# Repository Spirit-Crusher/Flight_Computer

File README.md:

MCU: https://www.microchip.com/en-us/product/pic32mz2048efh100

GPS: https://pt.mouser.com/ProductDetail/u-blox/NEO-M8J?qs=sGAEpiMZZMu3sxpa5v1qrlhWywTP0pnuh%2BmP8LamgMg%3D

Data logging for GPS: https://pt.mouser.com/ProductDetail/Microchip-Technology/SST26VF032BT-104I-SM?qs=wzzOUr4NhYqzScXXOX3HBA%3D%3D

IMU (acel + gyro): https://pt.mouser.com/ProductDetail/STMicroelectronics/LSM6DS3TR-C?qs=sGAEpiMZZMs29kr3d%2BndIw9GjDKvhDTryg6A%2FwXJ%2FS4%3D

Magnetómetro: https://pt.mouser.com/ProductDetail/STMicroelectronics/LIS3MDLTR?qs=hnsWAVXnr6EbLE48dGN9Pg%3D%3D

Altímetro (temp incluída): https://pt.mouser.com/ProductDetail/Measurement-Specialties/MS560702BA03-50?qs=sGAEpiMZZMtiz6SYu%2FjtS3nI99Ya1op5gwRqEQTw8xo%3D

Buzzer: https://www.digikey.com/en/products/detail/ole-wolff-electronics-inc/OWMB-858540SA-40-15/16735155

Antena(GPS): ???

Telemetry transmiter/antenna: ???

Data logging (flash memory IC): https://pt.mouser.com/ProductDetail/Winbond/W25Q128JVSIQ?qs=qSfuJ%252Bfl%2Fd6tLXvPR4fl9w%3D%3D

Power management IC: https://pt.mouser.com/ProductDetail/Texas-Instruments/INA219BIDR?qs=1WmUhT%2FVMINyGsXNJcdD5Q%3D%3D (maybe BMS board would be better)

Pyro channels and others

Ver redundância 

# DONE
- [x] Decoupling capacitors for each IC and basic conections.
- [ ] Sorting out power (all 3V3 or anything else needed?)
- [ ] Reverse polarity protection (which approach should I use?)
- [x] Programmer pins connector

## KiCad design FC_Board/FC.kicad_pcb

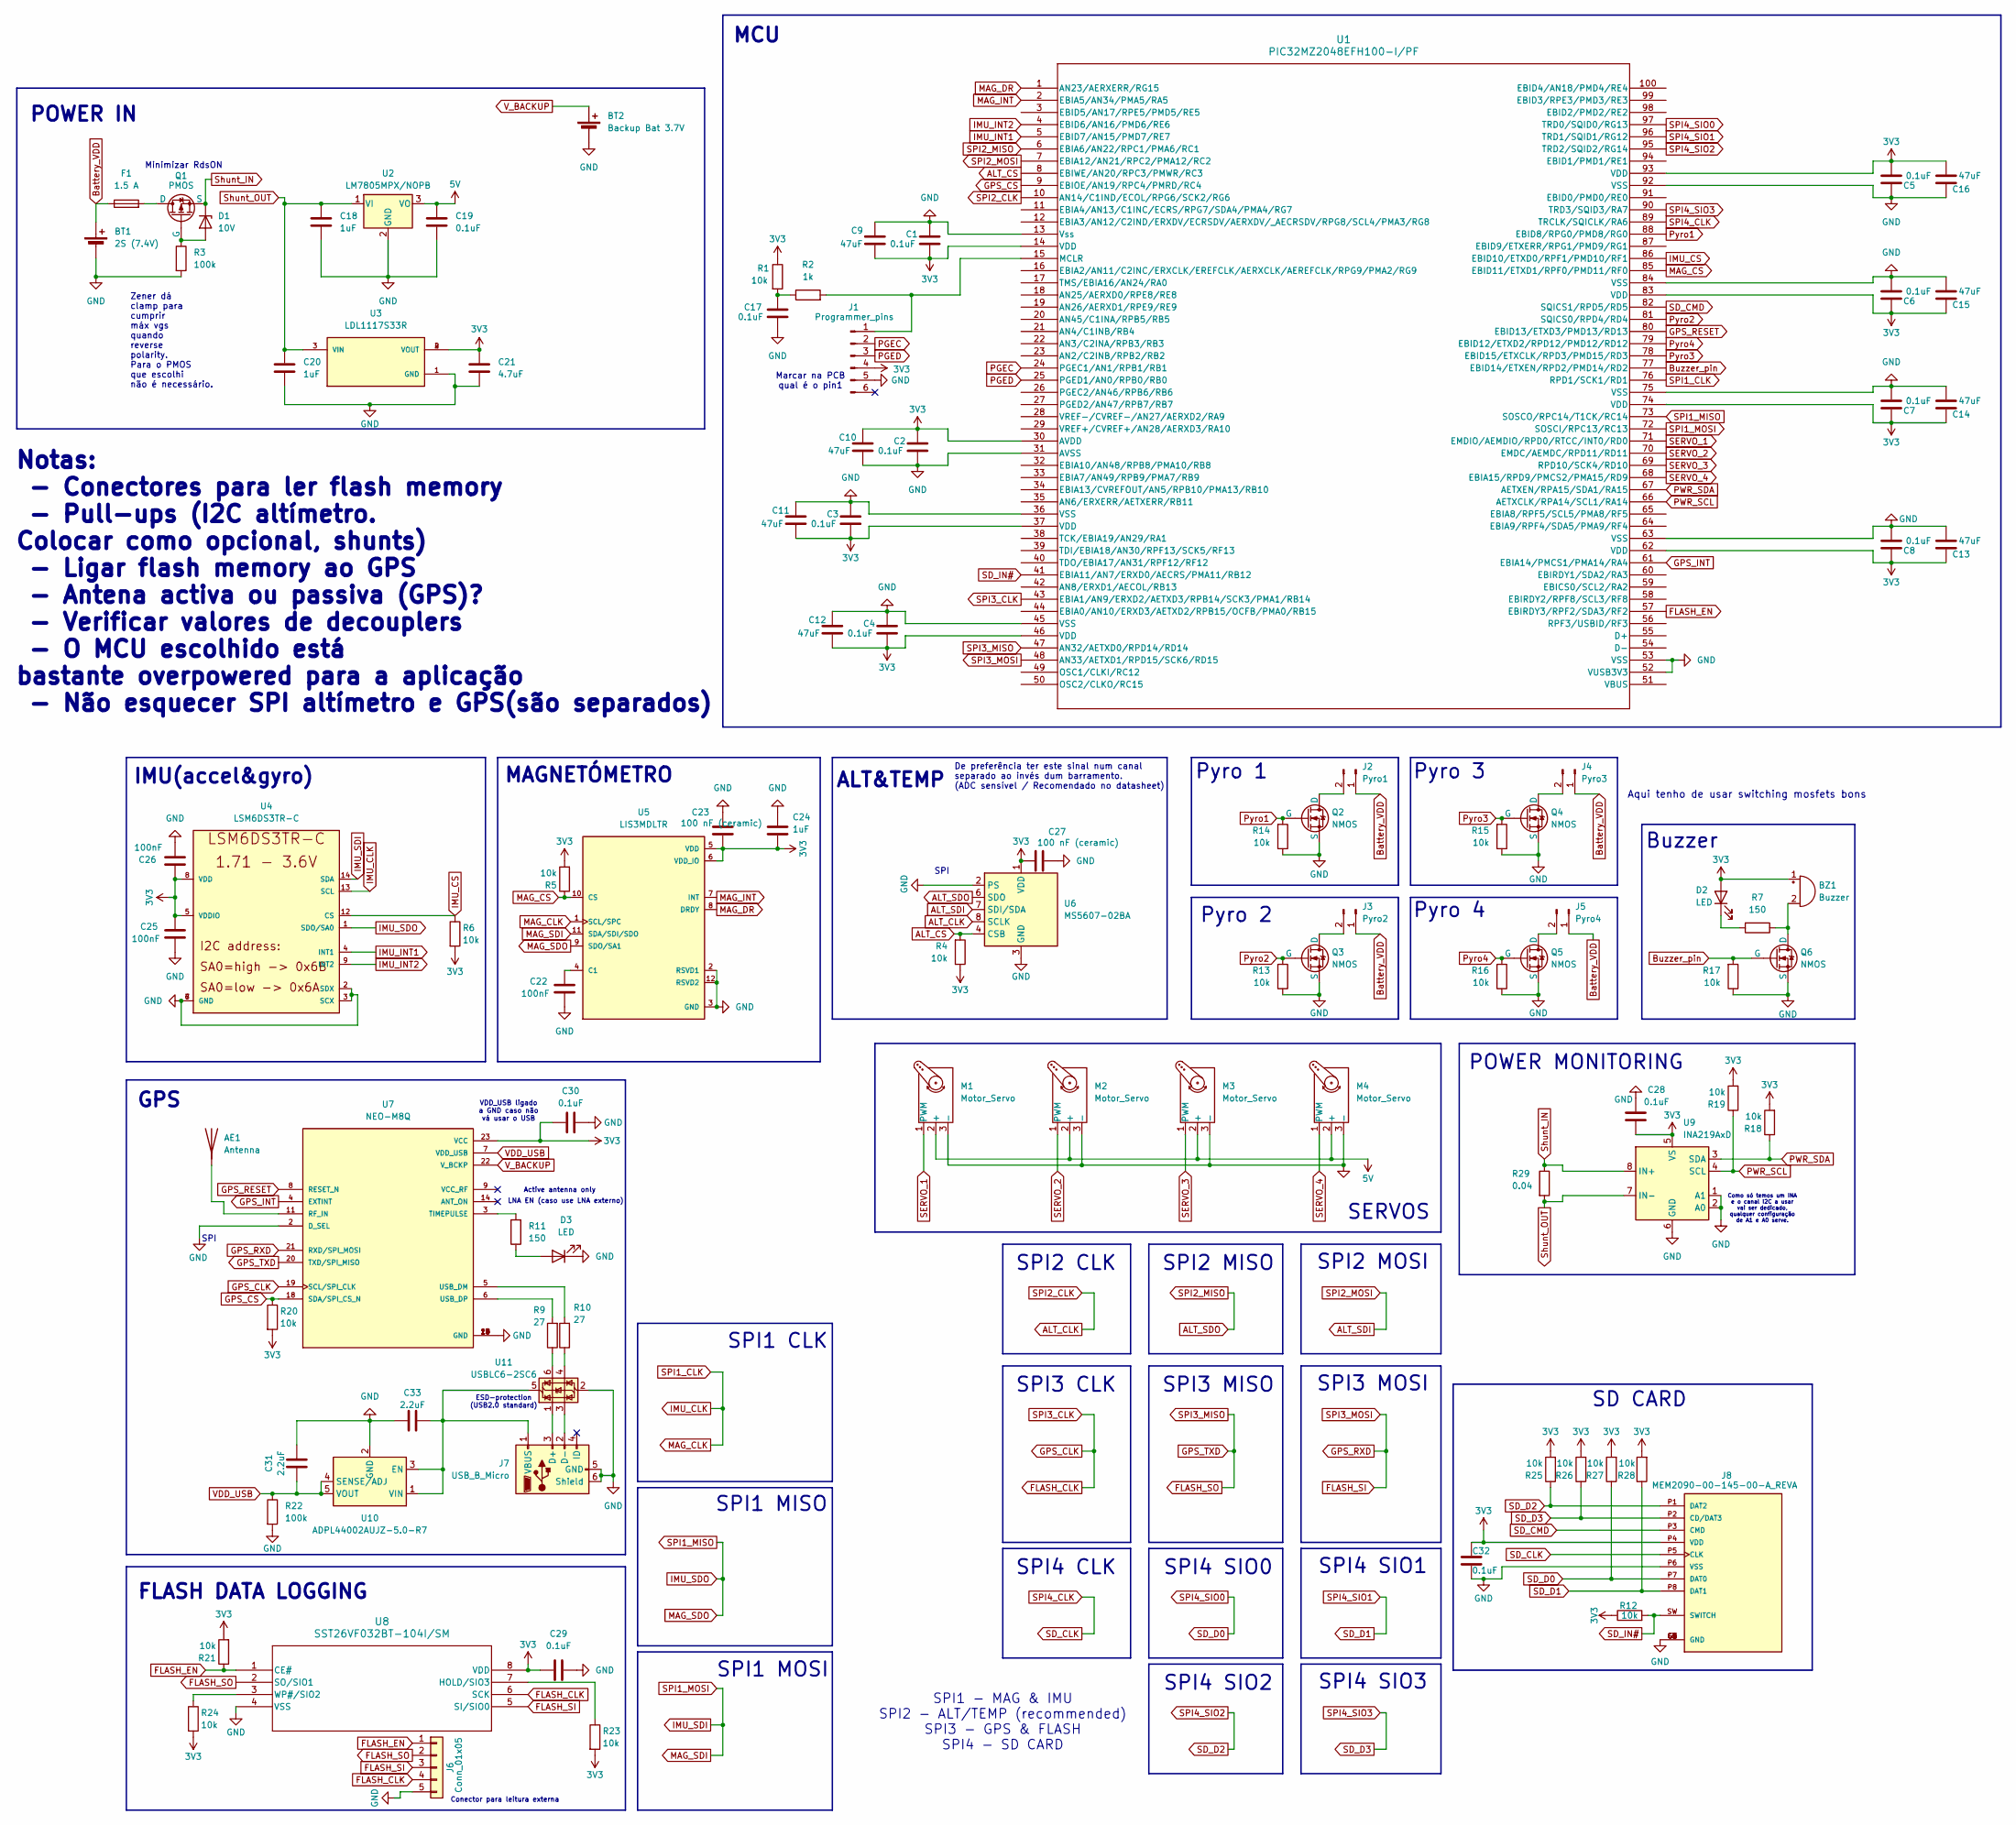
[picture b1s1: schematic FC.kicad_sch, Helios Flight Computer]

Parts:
AE1: Antenna; SMA_Samtec_SMA-J-P-H-ST-EM1_EdgeMount
BT1: 2S (7.4V); AMASS_XT60-M_1x02_P7.20mm_Vertical
BT2: Backup Bat 3.7V; JST_EH_B2B-EH-A_1x02_P2.50mm_Vertical
BZ1: Buzzer; Buzzer_12x9.5RM7.6
C1, C2, C3, C4, C5, C6, C7, C8, C17, C19, C28, C29, C30, C32: 0.1uF; C_0603_1608Metric_Pad1.08x0.95mm_HandSolder
C9, C10, C11, C12, C13, C14, C15, C16: 47uF; C_1210_3225Metric_Pad1.33x2.70mm_HandSolder
C18, C20, C24: 1uF; C_0603_1608Metric_Pad1.08x0.95mm_HandSolder
C21: 4.7uF; C_0805_2012Metric_Pad1.18x1.45mm_HandSolder
C22, C25, C26: 100nF; C_0603_1608Metric_Pad1.08x0.95mm_HandSolder
C23, C27: 100 nF (ceramic); C_0603_1608Metric_Pad1.08x0.95mm_HandSolder
C31, C33: 2.2uF; C_0603_1608Metric_Pad1.08x0.95mm_HandSolder
D1: 10V; D_SOD-323_HandSoldering
D2, D3: LED; LED_D3.0mm
F1: 1.5 A; Fuseholder_Cylinder-5x20mm_Schurter_0031_8201_Horizontal_Op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
J1: Programmer_pins; PinHeader_1x06_P2.54mm_Horizontal
J2: Pyro1; Molex_KK-254_AE-6410-02A_1x02_P2.54mm_Vertical
J3: Pyro2; Molex_KK-254_AE-6410-02A_1x02_P2.54mm_Vertical
J4: Pyro3; Molex_KK-254_AE-6410-02A_1x02_P2.54mm_Vertical
J5: Pyro4; Molex_KK-254_AE-6410-02A_1x02_P2.54mm_Vertical
J6: Conn_01x05; PinHeader_1x05_P2.54mm_Vertical
J7: USB_B_Micro; USB_Micro-B_Molex-105017-0001
J8: MEM2090-00-145-00-A_REVA; GCT_MEM2090-00-145-00-A_REVA; PARTREV A
M1, M2, M3, M4: Motor_Servo; Molex_KK-254_AE-6410-03A_1x03_P2.54mm_Vertical
Q1: PMOS; SOT-23-3
Q2, Q3, Q4, Q5, Q6: NMOS; SOT-23
R1, R4, R5, R6, R12, R13, R14, R15, R16, R17, R18, R19, R20, R21, R23, R24, R25, R26, R27, R28: 10k; R_0805_2012Metric_Pad1.20x1.40mm_HandSolder
R2: 1k; R_0805_2012Metric_Pad1.20x1.40mm_HandSolder
R3, R22: 100k; R_1206_3216Metric_Pad1.30x1.75mm_HandSolder
R7, R11: 150; R_0603_1608Metric_Pad0.98x0.95mm_HandSolder
R9, R10: 27; R_0603_1608Metric_Pad0.98x0.95mm_HandSolder
R29: 0.04; R_2512_6332Metric_Pad1.40x3.35mm_HandSolder
U1: PIC32MZ2048EFH100-I/PF; QFP50P1600X1600X120-100N
U2: LM7805MPX/NOPB; TO-220-3_Vertical
U3: LDL1117S33R; SOT230P700X180-4N; PARTREV 7
U4: LSM6DS3TR-C; LGA-14-2.5X3MM
U5: LIS3MDLTR; XDCR_LIS3MDLTR; PARTREV 6
U6: MS5607-02BA; LGA-8_3x5mm_P1.25mm
U7: NEO-M8Q; XCVR_NEO-M8Q; PARTREV 10
U8: SST26VF032BT-104I/SM; SOIC-8W_5.3x5.3mm_P1.27mm
U9: INA219AxD; SOIC-8_3.9x4.9mm_P1.27mm
U10: ADPL44002AUJZ-5.0-R7; TSOT-23-5
U11: USBLC6-2SC6; SOT-23-6

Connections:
3V3: BZ1.1 (+), C1.2, C2.1, C3.2, C4.2, C5.2, C6.1, C7.1, C8.1, C9.2, C10.1, C11.2, C12.2, C13.1, C14.1, C15.1, C16.2, C21.1, C23.2, C24.2, C25.1, C26.1, C27.2, C28.1, C29.2, C30.2, C32.1, D2.2 (A), J1.4, J8.P4 (VDD), R1.1, R4.1, R5.2, R6.2, R12.1, R18.2, R19.2, R20.2, R21.2, R23.2, R24.2, R25.2, R26.2, R27.2, R28.2, U1.14 (VDD), U1.30 (AVDD), U1.37 (VDD), U1.46 (VDD), U1.62 (VDD), U1.74 (VDD), U1.83 (VDD), U1.93 (VDD), U3.2 (VOUT), U3.4 (VOUT), U4.5 (VDDIO), U4.8 (VDD), U5.5 (VDD), U5.6 (VDD_IO), U6.1 (VDD), U7.23 (VCC), U8.8 (VDD), U9.5 (VS)
5V: C19.1, M1.2 (+), M2.2 (+), M3.2 (+), M4.2 (+), U2.3 (VO)
ALT_CLK: U1.10 (AN14/C1IND/ECOL/RPG6/SCK2/RG6), U6.8 (SCLK)
ALT_CS: R4.2, U1.8 (EBIWE/AN20/RPC3/PMWR/RC3), U6.4 (CSB), U6.5 (CSB)
ALT_SDI: U1.7 (EBIA12/AN21/RPC2/PMA12/RC2), U6.7 (SDI/SDA)
ALT_SDO: U1.6 (EBIA6/AN22/RPC1/PMA6/RC1), U6.6 (SDO)
Battery_VDD: BT1.1 (+), F1.1, J2.1, J3.1, J4.1, J5.1
Buzzer_pin: Q6.2 (G), R17.2, U1.77 (EBID14/ETXEN/RPD2/PMD14/RD2)
FLASH_CLK: J6.4, U1.43 (EBIA1/AN9/ERXD2/AETXD3/RPB14/SCK3/PMA1/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), U7.19 (SCL/SPI_CLK), U8.6 (SCK)
FLASH_EN: J6.1, R21.1, U1.57 (EBIRDY3/RPF2/SDA3/RF2), U8.1 (CE#)
FLASH_SI: J6.3, U1.48 (AN33/AETXD1/RPD15/SCK6/RD15), U7.21 (RXD/SPI_MOSI), U8.5 (SI/SIO0)
FLASH_SO: J6.2, U1.47 (AN32/AETXD0/RPD14/RD14), U7.20 (TXD/SPI_MISO), U8.2 (SO/SIO1)
GND: BT1.2 (-), BT2.2 (-), C1.1, C2.2, C3.1, C4.1, C5.1, C6.2, C7.2, C8.2, C9.1, C10.2, C11.1, C12.1, C13.2, C14.2, C15.2, C16.1, C17.2, C18.2, C19.2, C20.2, C21.2, C22.2, C23.1, C24.1, C25.2, C26.2, C27.1, C28.2, C29.1, C30.1, C31.2, C32.2, C33.1, D3.1 (K), J1.5, J6.5, J7.5 (GND), J7.6 (Shield), J8.G1 (GND), J8.G2 (GND), J8.G3 (GND), J8.G4 (GND), J8.G5 (GND), J8.G6 (GND), J8.P6 (VSS), M1.3 (-), M2.3 (-), M3.3 (-), M4.3 (-), Q2.3 (S), Q3.3 (S), Q4.3 (S), Q5.3 (S), Q6.3 (S), R3.2, R13.1, R14.1, R15.1, R16.1, R17.1, R22.2, U1.13 (Vss), U1.31 (AVSS), U1.36 (VSS), U1.45 (VSS), U1.52 (VUSB3V3), U1.53 (VSS), U1.63 (VSS), U1.75 (VSS), U1.84 (VSS), U1.92 (VSS), U2.2 (GND), U3.1 (GND), U4.2 (SDX), U4.3 (SCX), U4.6 (GND), U4.7 (GND), U5.2 (RSVD1), U5.3 (GND), U5.12 (RSVD2), U6.2 (PS), U6.3 (GND), U7.2 (D_SEL), U7.10 (GND), U7.12 (GND), U7.13 (GND), U7.24 (GND), U8.4 (VSS), U9.1 (A1), U9.2 (A0), U9.6 (GND), U10.2 (GND), U11.2 (GND)
GPS_CS: R20.1, U1.9 (EBIOE/AN19/RPC4/PMRD/RC4), U7.18 (SDA/SPI_CS_N)
GPS_INT: U1.61 (EBIA14/PMCS1/PMA14/RA4), U7.4 (EXTINT)
GPS_RESET: U1.80 (EBID13/ETXD3/PMD13/RD13), U7.8 (RESET_N)
IMU_CLK: U1.76 (RPD1/SCK1/RD1), U4.13 (SCL), U5.1 (SCL/SPC)
IMU_CS: R6.1, U1.86 (EBID10/ETXD0/RPF1/PMD10/RF1), U4.12 (CS)
IMU_INT1: U1.5 (EBID7/AN15/PMD7/RE7), U4.4 (INT1)
IMU_INT2: U1.4 (EBID6/AN16/PMD6/RE6), U4.9 (INT2)
IMU_SDI: U1.72 (SOSCI/RPC13/RC13), U4.14 (SDA), U5.11 (SDA/SDI/SDO)
IMU_SDO: U1.73 (SOSCO/RPC14/T1CK/RC14), U4.1 (SDO/SA0), U5.9 (SDO/SA1)
MAG_CS: R5.1, U1.85 (EBID11/ETXD1/RPF0/PMD11/RF0), U5.10 (CS)
MAG_DR: U1.1 (AN23/AERXERR/RG15), U5.8 (DRDY)
MAG_INT: U1.2 (EBIA5/AN34/PMA5/RA5), U5.7 (INT)
unnamed: AE1.1 (A), U7.11 (RF_IN)
unnamed: BZ1.2 (-), Q6.1 (D), R7.1
unnamed: C17.1, R1.2, R2.1
unnamed: D1.2 (A), Q1.2 (G), R3.1
unnamed: D2.1 (K), R7.2
unnamed: D3.2 (A), R11.1
unnamed: J1.1, R2.2, U1.15 (MCLR)
unnamed: J2.2, Q2.1 (D)
unnamed: J3.2, Q3.1 (D)
unnamed: J4.2, Q4.1 (D)
unnamed: J5.2, Q5.1 (D)
unnamed: J7.3 (D+), U11.1 (I/O1)
unnamed: J7.2 (D-), U11.3 (I/O2)
unnamed: C33.2, J7.1 (VBUS), U10.1 (VIN), U10.3 (EN), U11.5 (VBUS)
unnamed: F1.2, Q1.1 (D)
unnamed: R9.1, U11.6 (I/O1)
unnamed: R10.1, U11.4 (I/O2)
unnamed: C22.1, U5.4 (C1)
unnamed: R11.2, U7.3 (TIMEPULSE)
unnamed: R10.2, U7.5 (USB_DM)
unnamed: R9.2, U7.6 (USB_DP)
unnamed: R23.1, U8.7 (HOLD/SIO3)
unnamed: R24.1, U8.3 (WP#/SIO2)
PGEC: J1.2, U1.24 (PGEC1/AN1/RPB1/RB1)
PGED: J1.3, U1.25 (PGED1/AN0/RPB0/RB0)
PWR_SCL: R19.1, U1.66 (AETXCLK/RPA14/SCL1/RA14), U9.4 (SCL)
PWR_SDA: R18.1, U1.67 (AETXEN/RPA15/SDA1/RA15), U9.3 (SDA)
Pyro1: Q2.2 (G), R14.2, U1.88 (EBID8/RPG0/PMD8/RG0)
Pyro2: Q3.2 (G), R13.2, U1.81 (SQICS0/RPD4/RD4)
Pyro3: Q4.2 (G), R15.2, U1.78 (EBID15/ETXCLK/RPD3/PMD15/RD3)
Pyro4: Q5.2 (G), R16.2, U1.79 (EBID12/ETXD2/RPD12/PMD12/RD12)
SD_CLK: J8.P5 (CLK), U1.89 (TRCLK/SQICLK/RA6)
SD_CMD: J8.P3 (CMD), U1.82 (SQICS1/RPD5/RD5)
SD_D0: J8.P7 (DAT0), R27.1, U1.97 (TRD0/SQID0/RG13)
SD_D1: J8.P8 (DAT1), R28.1, U1.96 (TRD1/SQID1/RG12)
SD_D2: J8.P1 (DAT2), R25.1, U1.95 (TRD2/SQID2/RG14)
SD_D3: J8.P2 (CD/DAT3), R26.1, U1.90 (TRD3/SQID3/RA7)
SD_IN#: J8.SW (SWITCH), R12.2, U1.41 (EBIA11/AN7/ERXD0/AECRS/PMA11/RB12)
SERVO_1: M1.1 (PWM), U1.71 (EMDIO/AEMDIO/RPD0/RTCC/INT0/RD0)
SERVO_2: M2.1 (PWM), U1.70 (EMDC/AEMDC/RPD11/RD11)
SERVO_3: M3.1 (PWM), U1.69 (RPD10/SCK4/RD10)
SERVO_4: M4.1 (PWM), U1.68 (EBIA15/RPD9/PMCS2/PMA15/RD9)
Shunt_IN: D1.1 (K), Q1.3 (S), R29.1, U9.8 (IN+)
Shunt_OUT: C18.1, C20.1, R29.2, U2.1 (VI), U3.3 (VIN), U9.7 (IN-)
VDD_USB: C31.1, R22.1, U7.7 (VDD_USB), U10.4 (SENSE/ADJ), U10.5 (VOUT)
V_BACKUP: BT2.1 (+), U7.22 (V_BCKP)

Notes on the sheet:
Pyro 3
SPI3 CLK
SPI
MAGNETÓMETRO
Buzzer
FLASH DATA LOGGING
Aqui tenho de usar switching mosfets bons
SPI2 MOSI
Notas: - Conectores para ler flash memory - Pull-ups (I2C altímetro. Colocar como opcional, shunts) - Ligar flash memory ao GPS - Antena activa ou passiva (GPS)? - Verificar valores de decouplers - O MCU escolhido está bastante overpowered para a aplicação - Não esquecer SPI altímetro e GPS(são sep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
GPS
Pyro 2
IMU(accel&gyro)
SPI3 MISO
SPI1 MOSI
SERVOS
SPI1 - MAG & IMU SPI2 - ALT/TEMP (recommended) SPI3 - GPS & FLASH SPI4 - SD CARD
Zener dá clamp para cumprir máx vgs quando reverse polarity. Para o PMOS que escolhi não é necessário.
VDD_USB ligado a GND caso não vá usar o USB
Pyro 1
De preferência ter este sinal num canal separado ao invés dum barramento. (ADC sensível / Recomendado no datasheet)
ALT&TEMP
Minimizar RdsON
SD CARD
SPI1 MISO
Como só temos um INA e o canal I2C a usar vai ser dedicado, qualquer configuração de A1 e A0 serve.
SPI2 MISO
ESD-protection (USB2.0 standard)
Conector para leitura externa
Marcar na PCB qual é o pin1
SPI4 SIO0
SPI4 SIO3
SPI2 CLK
SPI4 SIO1
POWER MONITORING
Pyro 4
SPI4 CLK
LNA EN (caso use LNA externo)
MCU
Active antenna only
SPI1 CLK

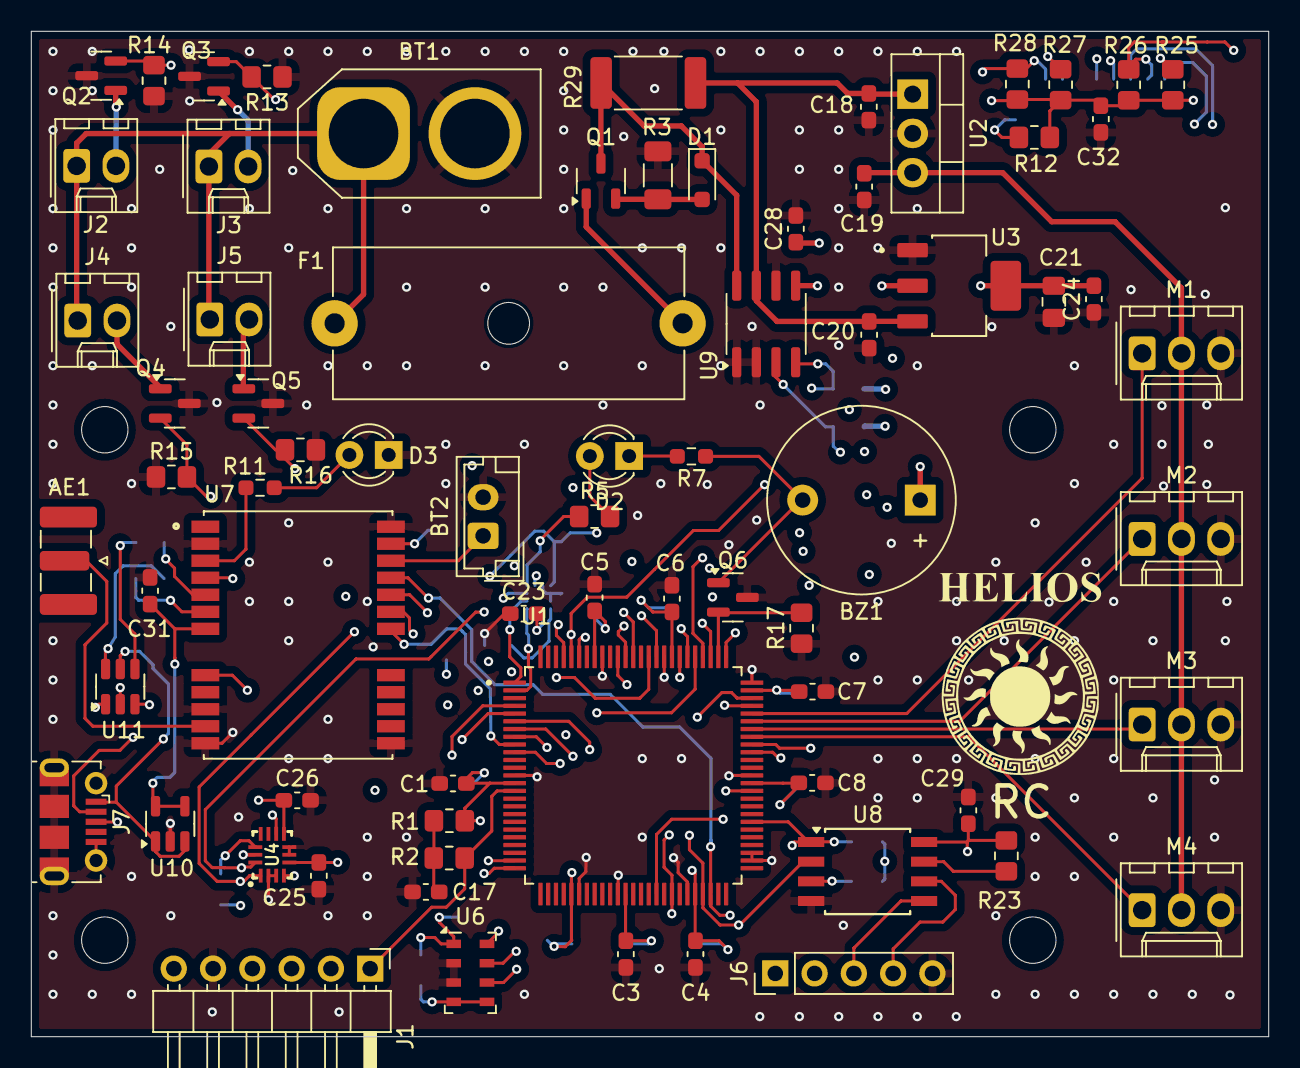
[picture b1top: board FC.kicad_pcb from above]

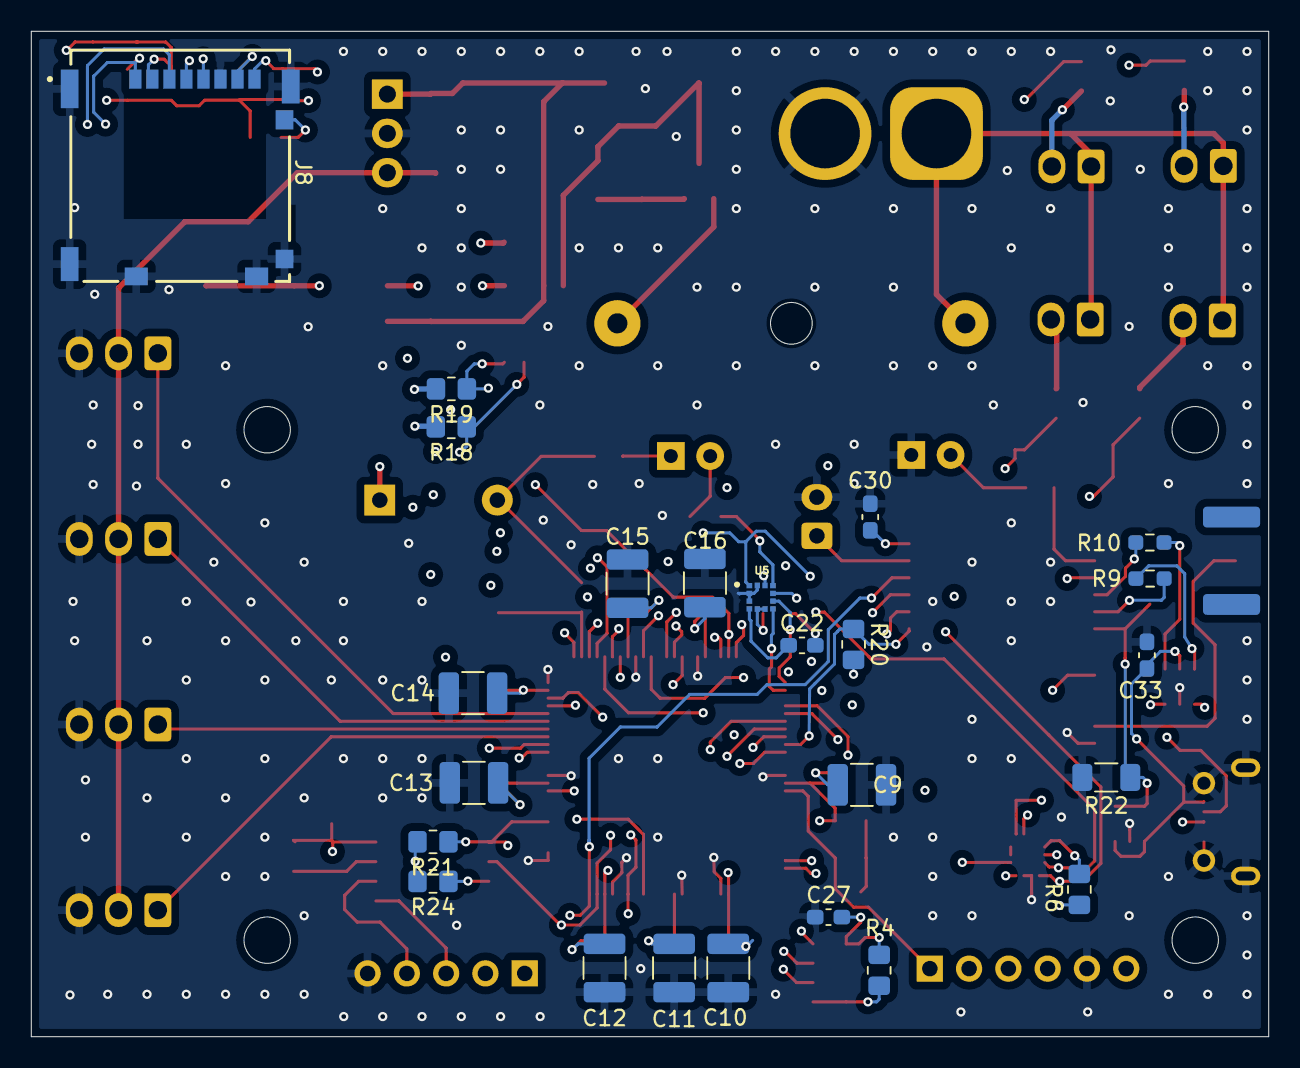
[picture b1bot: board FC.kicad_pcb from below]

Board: 4 copper layers, 80.0 x 65.0 mm, 97 parts (24 on the bottom side), 71 nets.

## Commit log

2024-10-13 Added datasheets and footprints/symbols
2024-10-15 Added IC decoupling and basic connections
2025-01-11 Schematic progress
    GPS data logging, Power monitoring and other updates to schematic.
2025-01-12 Added SD card and some other basic stuff
2025-07-09 Schematic update
    - Add: PWM level shifting
    - Add: SPI bus
    - Add: buzzer drain setup
    - Update: 5V power for servos
    - Verify: LDO sizing
2025-07-10 Schematic update
    - Remove: Buffers on PWM unnecessary (internal servo logic handles 3V3)
    - Add: Selecting PIC pins for SPI bus and sensor interrupts
    - Other minor tweaks
2025-07-12 Power monitoring done
2025-07-12 Schematic update
    - Add: SPI2 channel
    - Add: INA I2C connections
    - Component selection
2025-07-12 Schematic update
    - Add: GPS USB and UART
    - Add: USB 2.0 standard related circuitry
    - Finished third SPI Bus
    - Started Quad SPI Bus for data logging (SD card and Flash)
2025-07-13 Schematic Done
2025-07-14 Started PCB
2025-07-14 First placement attempt
2025-07-14 Transitioning to 4 layers
    Tried 2 layer routing to minimize cost. Too many tracks...
2025-08-18 Routing done except for gnd vias
2025-09-04 Helios_v1.0 DONE
